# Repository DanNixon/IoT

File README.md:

# IoT

Various internet of things related devices and projects.

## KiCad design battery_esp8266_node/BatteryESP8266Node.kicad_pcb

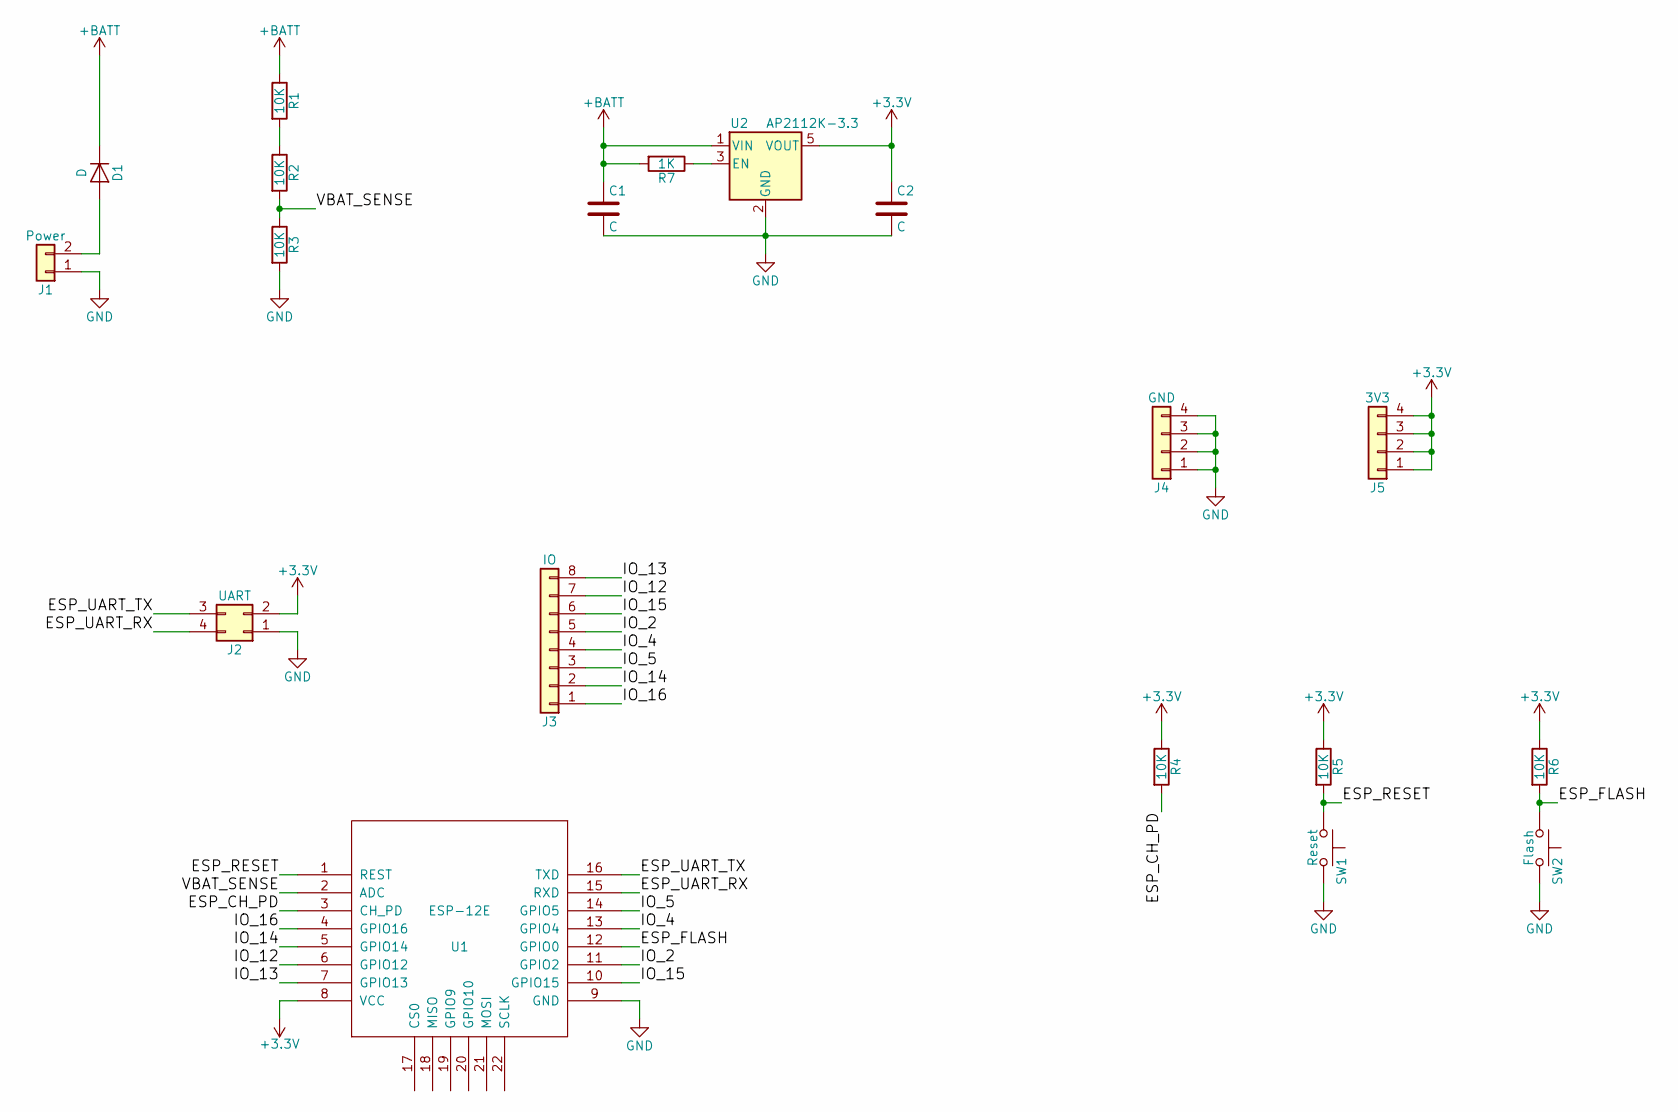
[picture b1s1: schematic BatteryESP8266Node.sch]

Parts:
C1, C2: C; C_0805
D1: D; D_0805
J1: Power; Pin_Header_Straight_1x02_Pitch2.54mm
J2: UART; Pin_Header_Straight_2x02_Pitch2.54mm
J3: IO; Pin_Header_Straight_1x08_Pitch2.54mm
J4: GND; Pin_Header_Straight_1x04_Pitch2.54mm
J5: 3V3; Pin_Header_Straight_1x04_Pitch2.54mm
R1, R2, R3, R4, R5, R6: 10K; R_0805
R7: 1K; R_0805
SW1: Reset; SW_SPST_KMR2
SW2: Flash; SW_SPST_KMR2
U1: ESP-12E; ESP-12E_SMD
U2: AP2112K-3.3; SOT-23-5

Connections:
+3V3: C2.1, J2.2, J5.1, J5.2, J5.3, J5.4, R4.1, R5.1, R6.1, U1.8 (VCC), U2.5 (VOUT)
+BATT: C1.1, D1.1 (K), R1.1, R7.2, U2.1 (VIN)
/ESP_CH_PD: R4.2, U1.3 (CH_PD)
/ESP_FLASH: R6.2, SW2.1, U1.12 (GPIO0)
/ESP_RESET: R5.2, SW1.1, U1.1 (REST)
/ESP_UART_RX: J2.4, U1.15 (RXD)
/ESP_UART_TX: J2.3, U1.16 (TXD)
/IO_2: J3.5, U1.11 (GPIO2)
/IO_4: J3.4, U1.13 (GPIO4)
/IO_5: J3.3, U1.14 (GPIO5)
/IO_12: J3.7, U1.6 (GPIO12)
/IO_13: J3.8, U1.7 (GPIO13)
/IO_14: J3.2, U1.5 (GPIO14)
/IO_15: J3.6, U1.10 (GPIO15)
/IO_16: J3.1, U1.4 (GPIO16)
/VBAT_SENSE: R2.2, R3.1, U1.2 (ADC)
GND: C1.2, C2.2, J1.1, J2.1, J4.1, J4.2, J4.3, J4.4, R3.2, SW1.2, SW2.2, U1.9 (GND), U2.2 (GND)
unnamed: D1.2 (A), J1.2
unnamed: R1.2, R2.1
unnamed: R7.1, U2.3 (EN)

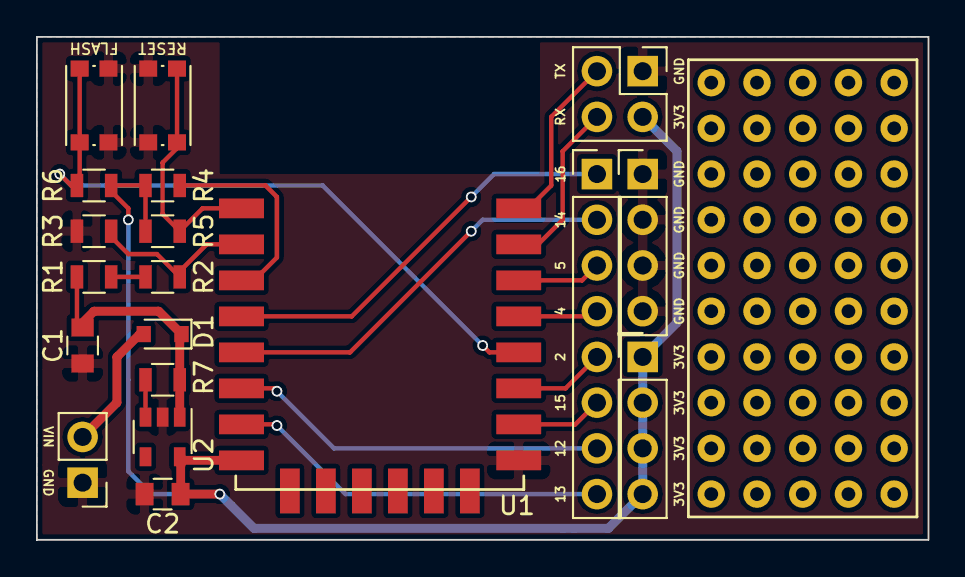
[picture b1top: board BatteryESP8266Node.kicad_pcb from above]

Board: 2 copper layers, 49.5 x 27.9 mm, 19 parts (0 on the bottom side), 20 nets.

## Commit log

2016-08-31 add exercise bike project
2016-08-31 blank firmware
2016-08-31 initial enclosure
2016-08-31 add oled
2016-08-31 switch to new display lib
2016-09-29 relay board
2016-09-29 add enclosure add more protocol options
2016-09-29 firmware updates
2017-10-11 Add Flan wings badge firmware
2017-10-14 Remove hardcoded lib dir
2017-10-29 Add generic neopixel light fixture
2017-10-29 Add sample config
2017-11-04 Add DHT22 sensor to flan wings
2017-11-05 Add DHT node for HA
2017-11-05 Restructure
2017-11-06 Add KiCad ignore rules
2017-11-12 Remove incomplete project
2017-11-12 Rename to common convention
2017-11-18 ESP8266 node hardware
    Schematic and first board revision
2017-11-18 Use library as submodule
2017-11-18 Second board revision
    All components on a single side, generally neater layout, added proto
    headers.
2017-11-18 Add prototyping area
2017-11-18 Reduce board size slightly and add dimensions
2017-11-19 Add silkscreen, final check
2017-12-02 garage node
2017-12-02 Remove LEDs from garage node
2017-12-02 Correct state
2018-03-10 Add broadlink remote codes
2018-03-13 DHT node updates
2018-03-24 Add old Optoma projector
2018-03-24 Add missing config.h file
2018-04-15 Add generic IR fan
2018-05-07 Add wemos stack demo
2018-05-07 Fix a couple of issues
    - nan values not playing nicely with HA
    - availabilty reporting as offline when rebooted
2018-05-13 Update garage monitor
2018-05-20 Wemos climate node
